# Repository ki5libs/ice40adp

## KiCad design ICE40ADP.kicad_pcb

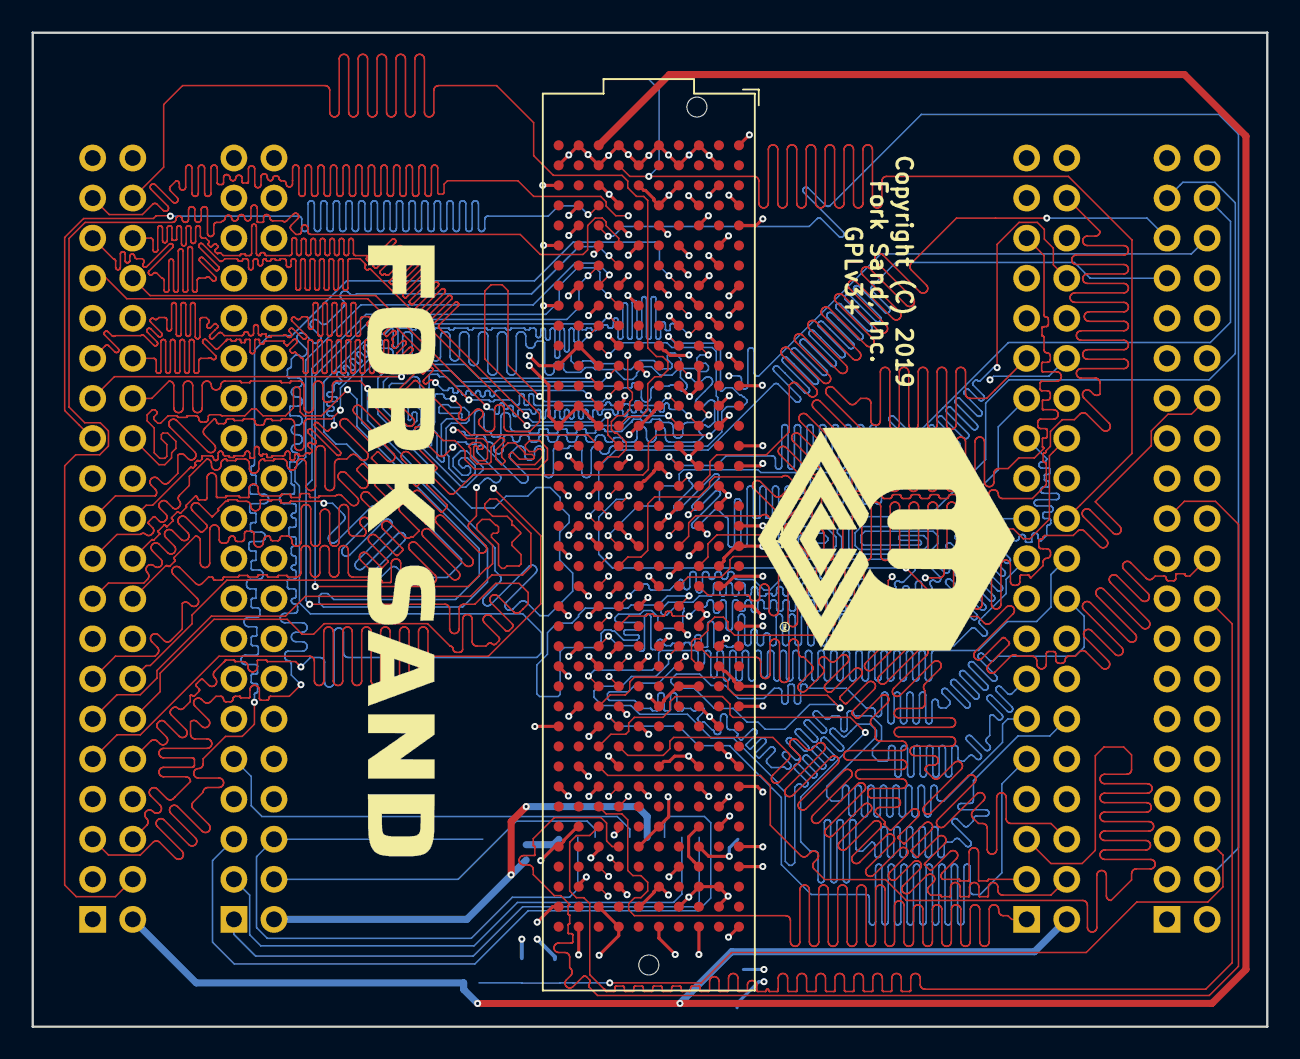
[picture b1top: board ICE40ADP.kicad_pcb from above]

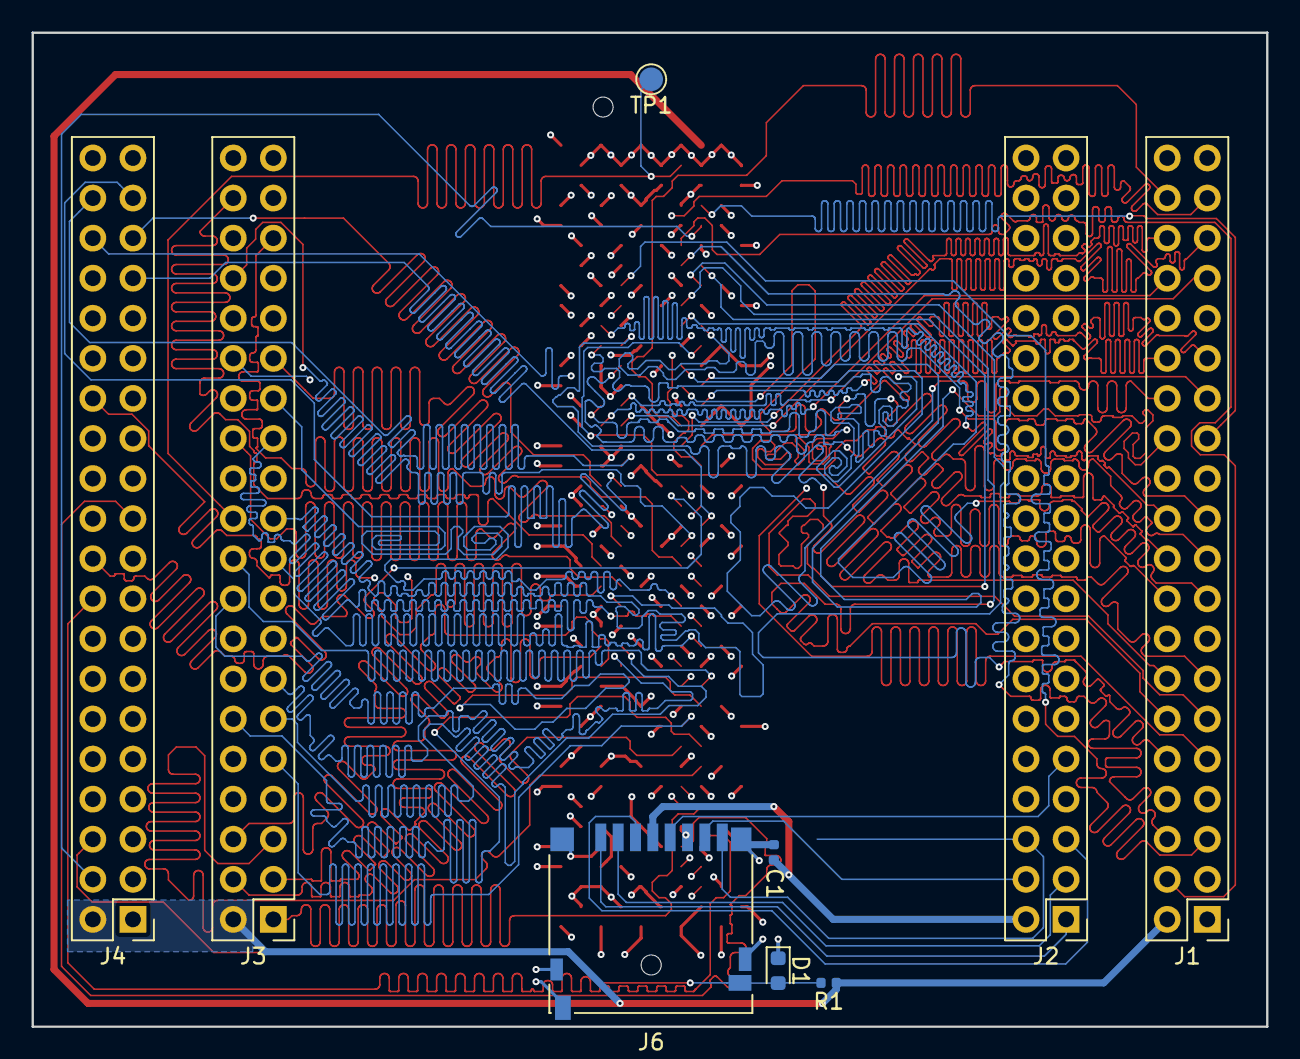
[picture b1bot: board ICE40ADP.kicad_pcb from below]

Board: 4 copper layers, 78.3 x 63.0 mm, 10 parts (9 on the bottom side), 82 nets.

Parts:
C1: 4.7uF; C_0402_1005Metric
D1: PGB1010603NRHF; D_0603_1608Metric
J1, J2, J3, J4: Conn_02x20_Odd_Even; PinHeader_2x20_P2.54mm_Vertical
J5: Samtec_ASP-134486-01; Samtec_FMC_ASP-134486-01_10x40_P1.27mm_Vertical
J6: Micro_SD_Card_Det; microSD_HC_Hirose_DM3D-SF
R1: 100K; R_0402_1005Metric
TP1: TestPoint; TestPoint_Pad_D1.5mm

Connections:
+1V8: J1.2, J3.2, J4.2, J5.H1, R1.1
/Sheet5CA0FCBB/+3V3: C1.1, J2.2, J6.4
/Sheet5CA0FCBB/SDIO_CD: D1.2, J4.6, J6.9, R1.2
/Sheet5CA0FCBB/SDIO_CLK: J2.9, J6.5
/Sheet5CA0FCBB/SDIO_CMD: J2.5, J6.3
/Sheet5CA0FCBB/SDIO_DAT0: J2.4, J6.7
/Sheet5CA0FCBB/SDIO_DAT1: J2.6, J6.8
/Sheet5CA0FCBB/SDIO_DAT2: J2.1, J6.1
/Sheet5CA0FCBB/SDIO_DAT3: J2.3, J6.2
/Sheet5CA0FCF5/12P0V_FMC: J5.C35, J5.C37
CHIPLINK_RX_CLK: J3.22, J5.G2, TP1.1
CHIPLINK_RX_DAT0: J3.37, J5.D20
CHIPLINK_RX_DAT1: J3.35, J5.D21
CHIPLINK_RX_DAT2: J3.38, J5.C22
CHIPLINK_RX_DAT3: J3.33, J5.C23
CHIPLINK_RX_DAT4: J3.30, J5.H22
CHIPLINK_RX_DAT5: J3.36, J5.H23
CHIPLINK_RX_DAT6: J3.34, J5.G21
CHIPLINK_RX_DAT7: J3.29, J5.G22
CHIPLINK_RX_DAT8: J3.28, J5.H25
CHIPLINK_RX_DAT9: J3.19, J5.H26
CHIPLINK_RX_DAT10: J3.27, J5.G24
CHIPLINK_RX_DAT11: J3.25, J5.G25
CHIPLINK_RX_DAT12: J3.26, J5.D23
CHIPLINK_RX_DAT13: J3.21, J5.D24
CHIPLINK_RX_DAT14: J3.20, J5.H28
CHIPLINK_RX_DAT15: J3.18, J5.H29
CHIPLINK_RX_DAT16: J3.14, J5.G27
CHIPLINK_RX_DAT17: J3.17, J5.G28
CHIPLINK_RX_DAT18: J3.11, J5.D26
CHIPLINK_RX_DAT19: J3.13, J5.D27
CHIPLINK_RX_DAT20: J3.3, J5.C26
CHIPLINK_RX_DAT21: J3.6, J5.C27
CHIPLINK_RX_DAT22: J3.12, J5.H31
CHIPLINK_RX_DAT23: J3.5, J5.H32
CHIPLINK_RX_DAT24: J3.9, J5.G30
CHIPLINK_RX_DAT25: J3.4, J5.G31
CHIPLINK_RX_DAT26: J3.1, J5.H34
CHIPLINK_RX_DAT27: J4.18, J5.H35
CHIPLINK_RX_DAT28: J4.29, J5.G33
CHIPLINK_RX_DAT29: J4.27, J5.G34
CHIPLINK_RX_DAT30: J4.30, J5.H37
CHIPLINK_RX_DAT31: J4.25, J5.H38
CHIPLINK_RX_RST: J4.26, J5.G37
CHIPLINK_RX_SEND: J4.21, J5.G36
CHIPLINK_TX_CLK: J1.25, J5.H4
CHIPLINK_TX_DAT0: J1.4, J5.G6
CHIPLINK_TX_DAT1: J1.6, J5.G7
CHIPLINK_TX_DAT2: J1.5, J5.D8
CHIPLINK_TX_DAT3: J1.9, J5.D9
CHIPLINK_TX_DAT4: J1.11, J5.H7
CHIPLINK_TX_DAT5: J1.10, J5.H8
CHIPLINK_TX_DAT6: J1.12, J5.G9
CHIPLINK_TX_DAT7: J1.17, J5.G10
CHIPLINK_TX_DAT8: J1.21, J5.H10
CHIPLINK_TX_DAT9: J1.13, J5.H11
CHIPLINK_TX_DAT10: J1.14, J5.D11
CHIPLINK_TX_DAT11: J1.18, J5.D12
CHIPLINK_TX_DAT12: J1.22, J5.C10
CHIPLINK_TX_DAT13: J1.27, J5.C11
CHIPLINK_TX_DAT14: J1.26, J5.H13
CHIPLINK_TX_DAT15: J1.29, J5.H14
CHIPLINK_TX_DAT16: J1.28, J5.G12
CHIPLINK_TX_DAT17: J1.19, J5.G13
CHIPLINK_TX_DAT18: J1.33, J5.D14
CHIPLINK_TX_DAT19: J1.35, J5.D15
CHIPLINK_TX_DAT20: J1.20, J5.C14
CHIPLINK_TX_DAT21: J1.34, J5.C15
CHIPLINK_TX_DAT22: J1.30, J5.H16
CHIPLINK_TX_DAT23: J1.37, J5.H17
CHIPLINK_TX_DAT24: J1.38, J5.G15
CHIPLINK_TX_DAT25: J1.36, J5.G16
CHIPLINK_TX_DAT26: J4.38, J5.D17
CHIPLINK_TX_DAT27: J4.37, J5.D18
CHIPLINK_TX_DAT28: J4.35, J5.C18
CHIPLINK_TX_DAT29: J4.36, J5.C19
CHIPLINK_TX_DAT30: J4.34, J5.H19
CHIPLINK_TX_DAT31: J4.33, J5.H20
CHIPLINK_TX_RST: J4.20, J5.G19
CHIPLINK_TX_SEND: J4.28, J5.G18
Earth: C1.2, D1.1, J1.7, J1.8, J1.15, J1.16, J1.23, J1.24, J1.31, J1.32, J1.39, J1.40, J2.7, J2.8, J2.15, J2.16, J2.23, J2.24, J2.31, J2.32, J2.39, J2.40, J3.7, J3.8, J3.15, J3.16, J3.23, J3.24, J3.31, J3.32, J3.39, J3.40, J4.7, J4.8, J4.15, J4.16, J4.23, J4.24, J4.31, J4.32, J4.39, J4.40, J5.A1, J5.A4, J5.A5, J5.A8, J5.A9, J5.A12, J5.A13, J5.A16, J5.A17, J5.A20, J5.A21, J5.A24, J5.A25, J5.A28, J5.A29, J5.A32, J5.A33, J5.A36, J5.A37, J5.A40, J5.B2, J5.B3, J5.B6, J5.B7, J5.B10, J5.B11, J5.B14, J5.B15, J5.B18, J5.B19, J5.B22, J5.B23, J5.B26, J5.B27, J5.B30, J5.B31, J5.B34, J5.B35, J5.B38, J5.B39, J5.C1, J5.C4, J5.C5, J5.C8, J5.C9, J5.C12, J5.C13, J5.C16, J5.C17, J5.C20, J5.C21, J5.C24, J5.C25, J5.C28, J5.C29, J5.C32, J5.C33, J5.C36, J5.C38, J5.C40, J5.D2, J5.D3, J5.D6, J5.D7, J5.D10, J5.D13, J5.D16, J5.D19, J5.D22, J5.D25, J5.D28, J5.D37, J5.D39, J5.E1, J5.E4, J5.E5, J5.E8, J5.E11, J5.E14, J5.E17, J5.E20, J5.E23, J5.E26, J5.E29, J5.E32, J5.E35, J5.E38, J5.E40, J5.F2, J5.F3, J5.F6, J5.F9, J5.F12, J5.F15, J5.F18, J5.F21, J5.F24, J5.F27, J5.F30, J5.F33, J5.F36, J5.F39, J5.G1, J5.G4, J5.G5, J5.G8, J5.G11, J5.G14, J5.G17, J5.G20, J5.G23, J5.G26, J5.G29, J5.G32, J5.G35, J5.G38, J5.G40, J5.H2, J5.H3, J5.H6, J5.H9, J5.H12, J5.H15, J5.H18, J5.H21, J5.H24, J5.H27, J5.H30, J5.H33, J5.H36, J5.H39, J5.J1, J5.J4, J5.J5, J5.J8, J5.J11, J5.J14, J5.J17, J5.J20, J5.J23, J5.J26, J5.J29, J5.J32, J5.J35, J5.J38, J5.J40, J5.K2, J5.K3, J5.K6, J5.K9, J5.K12, J5.K15, J5.K18, J5.K21, J5.K24, J5.K27, J5.K30, J5.K33, J5.K36, J5.K39, J6.6, J6.10, J6.11
RESET_N: J4.4, J5.H5

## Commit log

2019-03-31 Connectors placement
2019-04-01 FMC lines
2019-04-07 LP lines added. Changed PCB connectors placement
2019-04-18 First version of routing
2020-03-12 Production version #1

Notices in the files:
ICE40ADP.kicad_pcb:
Copyright (C) 2019
GPLv3+
